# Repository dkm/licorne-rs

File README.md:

# Licorne Smart Alarm Clock

The firmware is pure Rust using [RTIC](https://rtic.rs/)(Real-Time Interrupt-driven Concurrency).

Objectives:
* allow for small kids to be aware of different day period using a simple color code (ie. 5:00 is sleep time).
* continue to learn embedded Rust
* have fun

## Features

* 2.13'in E-Paper display
* DS3231 RTC for keeping track of time
* BME680 for temperature and COV measures
* TI TM4C123G (Cortex M4F)

## Build log

The project initially started during first French lock-down because we really
needed our sleep time and the ours kids could not make the difference between
5:00 and 8:00. A first [Arduino
prototype](https://github.com/dkm/licorne-smartalarmclock) came to life quickly
and has been used for several months. In parallel, this project started with no
hard deadline with the following goals:
- have a more finished hardware solution (versus previous arduino breadboard)
- use event-based programming using embedded Rust

## PCB

## Software

## End result

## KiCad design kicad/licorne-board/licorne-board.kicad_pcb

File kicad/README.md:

# Simple Kicad file for making the board using Toner Transfer.

## Reused resources

custom.lib and custom.pretty extracted from Neotron Hardware:
https://github.com/Neotron-Compute/Neotron-32-Hardware/ for the EK-TM4C123GXL
board symbol and footprint.

Both items are covered by Creative Commons [CC-BY-SA 4.0]:

```
This schematic and PCB design is Copyright (c) Jonathan 'theJPster' Pallant and other Neotron 32 contributors.

This work is licensed under a Creative Commons Attribution-ShareAlike 4.0 International License.
```
[CC-BY-SA 4.0]:https://creativecommons.org/licenses/by-sa/4.0/legalcode

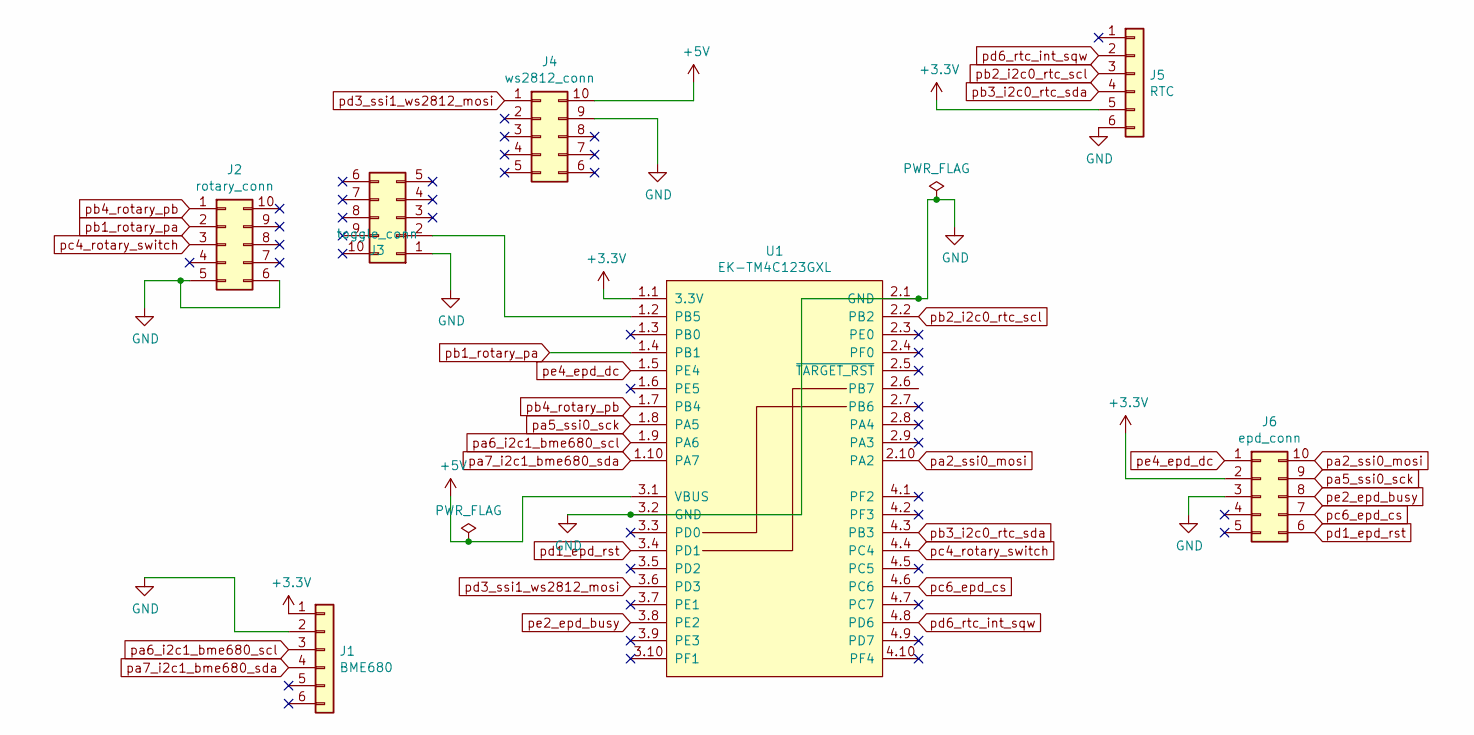
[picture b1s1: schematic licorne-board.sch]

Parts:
J1: BME680; PinHeader_1x06_P2.54mm_Vertical
J2: rotary_conn; IDC-Header_2x05_P2.54mm_Vertical
J3: toggle_conn; IDC-Header_2x05_P2.54mm_Vertical
J4: ws2812_conn; IDC-Header_2x05_P2.54mm_Vertical
J5: RTC; PinHeader_1x06_P2.54mm_Vertical
J6: epd_conn; IDC-Header_2x05_P2.54mm_Vertical
U1: EK-TM4C123GXL; Launchpad_4x10

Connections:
+3V3: J1.1, J5.5, J6.2, U1.1.1 (3.3V)
+5V: J4.10, U1.3.1 (VBUS)
GND: J1.2, J2.5, J2.6, J3.1, J4.9, J5.6, J6.3, U1.2.1 (GND), U1.3.2 (GND)
unnamed: J3.2, U1.1.2 (PB5)
pa2_ssi0_mosi: J6.10, U1.2.10 (PA2)
pa5_ssi0_sck: J6.9, U1.1.8 (PA5)
pa6_i2c1_bme680_scl: J1.3, U1.1.9 (PA6)
pa7_i2c1_bme680_sda: J1.4, U1.1.10 (PA7)
pb1_rotary_pa: J2.2, U1.1.4 (PB1)
pb2_i2c0_rtc_scl: J5.3, U1.2.2 (PB2)
pb3_i2c0_rtc_sda: J5.4, U1.4.3 (PB3~)
pb4_rotary_pb: J2.1, U1.1.7 (PB4)
pc4_rotary_switch: J2.3, U1.4.4 (PC4)
pc6_epd_cs: J6.7, U1.4.6 (PC6)
pd1_epd_rst: J6.6, U1.3.4 (PD1)
pd3_ssi1_ws2812_mosi: J4.1, U1.3.6 (PD3)
pd6_rtc_int_sqw: J5.2, U1.4.8 (PD6)
pe2_epd_busy: J6.8, U1.3.8 (PE2)
pe4_epd_dc: J6.1, U1.1.5 (PE4)

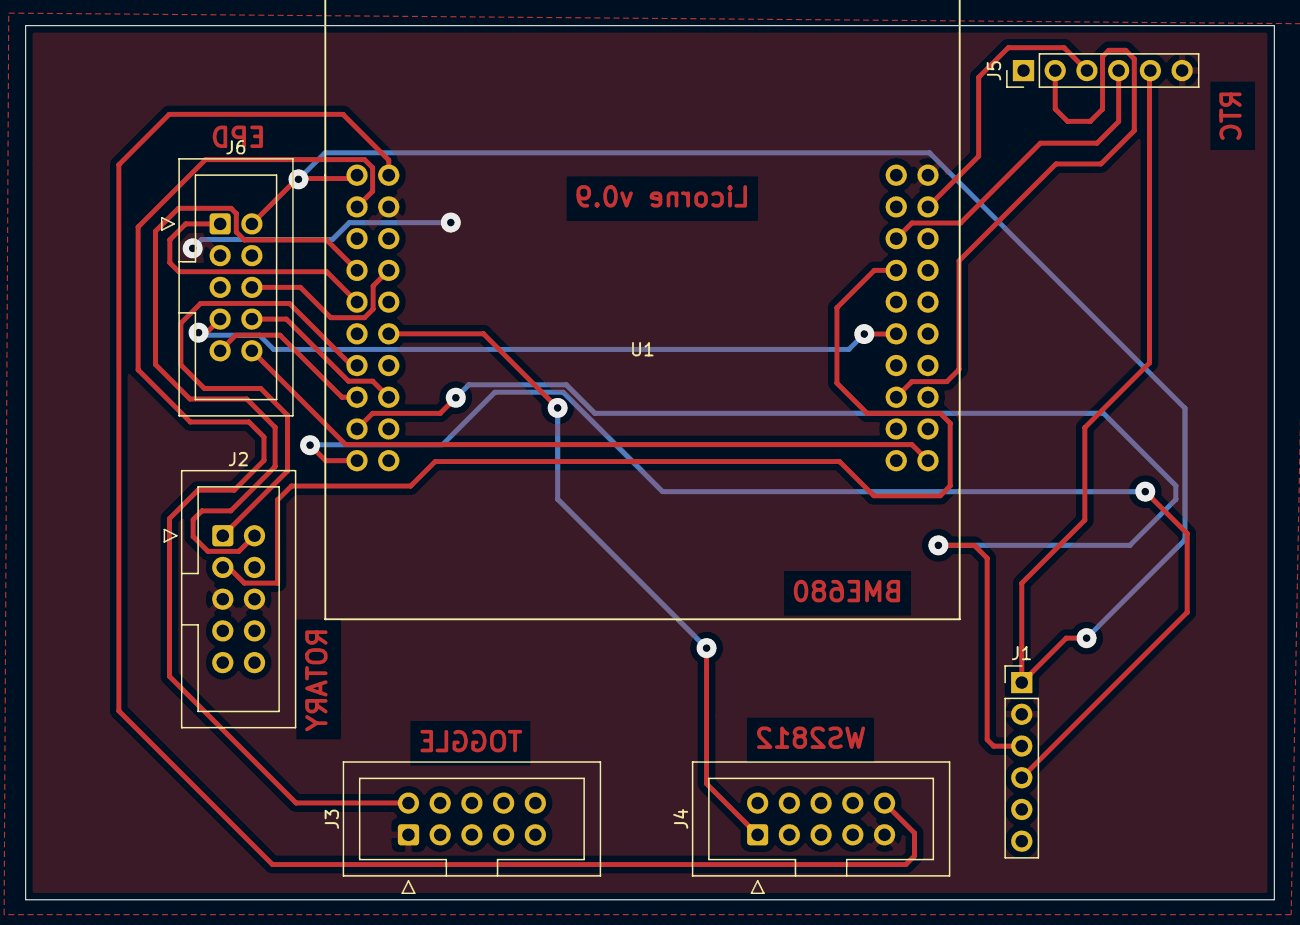
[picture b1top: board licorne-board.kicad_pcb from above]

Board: 2 copper layers, 100.0 x 70.0 mm, 7 parts (0 on the bottom side), 19 nets.

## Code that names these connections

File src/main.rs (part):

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    }
}

// Beware that PB7/PD1 and PB6/PD0 pairs are connected by a 0-ohm resistor
// You need to unsolder these R if you want to use both pins in a pair.
//
// PA2: SSI0 [epd]
// PA4: SSI0 [epd unconnected]
// PA5: SSI0 [epd]
// PA6: I2C1 (scl) [bme680]
// PA7: I2C1 (sca) [bme680]
//
//
// PB1: Rotary Encoder (pinA)
// PB2: I2C0 (SCL) [rtc]
// PB3: I2C0 (SDA) [rtc]
// PB4: Rotary Encoder (pinB)
// PB5: Toggle Switch (config mode)
// PB6:
// PC4: Rotary switch
//
// PC6: GPIO [EPD-cs]
//
// PD0: SSI1 [WS2812 unconnected]
// PD1: [EPD-reset]
// PD2: SSI1 [WS2812 unconnected]
// PD3: SSI1 [WS2812 DIN]
// PD6: RTC / INT
//
// PE2: GPIO Floating [EPD-busy]
// PE4: [EPD-dc]

use ds323x::{Ds323x, NaiveTime};
use tm4c123x_hal::{
    gpio::gpioa::{PA2, PA4, PA5, PA6, PA7},
    gpio::gpiob::{PB1, PB2, PB3, PB4, PB5},
    gpio::gpioc::{PC4, PC6},
    gpio::gpiod::{PD0, PD1, PD2, PD3},
    gpio::gpioe::{PE2, PE4},
    gpio::{
        AlternateFunction, Floating, Input, OpenDrain, Output, PullDown, PullUp, PushPull, AF2, AF3,
    },
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type I2c0T = I2c<
    I2C0,
    (
        PB2<AlternateFunction<AF3, PushPull>>,
        PB3<AlternateFunction<AF3, OpenDrain<Floating>>>,
    ),
>;

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type I2c1T = I2c<
    I2C1,
    (
        PA6<AlternateFunction<AF3, PushPull>>,
        PA7<AlternateFunction<AF3, OpenDrain<Floating>>>,
    ),
>;

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type Spi0T = Spi<
    SSI0,
    (
        PA2<AlternateFunction<AF2, PushPull>>,
        PA4<AlternateFunction<AF2, PushPull>>,
        PA5<AlternateFunction<AF2, PullDown>>,
    ),
>;

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    (
        PD0<AlternateFunction<AF2, PushPull>>,
        PD2<AlternateFunction<AF2, PushPull>>,
        PD3<AlternateFunction<AF2, PullDown>>,
    ),
>;

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
pub type EpdT = Epd2in13<
    Spi0T,
    PC6<Output<PushPull>>,
    PE2<Input<Floating>>,
    PE4<Output<PushPull>>,
    PD1<Output<PushPull>>,
    SimpleAsmDelay,
>;

type RotaryT = Rotary<PB1<Input<PullUp>>, PB4<Input<PullUp>>>;

#[derive(PartialEq)]
pub struct TimeRange {
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    brightness: u8,
}

type ToggleSwitchPinT = PB5<Input<PullUp>>;
type ToggleSwitchT = Switch<ToggleSwitchPinT>;

type RotarySwitchPinT = PC4<Input<PullUp>>;
type RotarySwitchT = Switch<RotarySwitchPinT>;

#[rtic::app(device = tm4c123x_hal::pac, peripherals = true, dispatchers = [UART1, UART2, UART3, UART4])]
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//    use rtic::cyccnt::Instant;

    use tm4c123x_hal::{
        gpio::{gpiod::PD6, Floating, GpioExt, Input, InterruptMode, PullUp, AF2, AF3},
        i2c::I2c,
        spi::{Spi, MODE_0},
        sysctl::{self, SysctlExt},
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        display_dirty: bool,

        #[cfg(feature = "rtc")]
        rtc_int_pin: PD6<Input<PullUp>>,

        // ws2812
        leds: LedsT,
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        let i2c_rtc_dev = I2c::i2c0(
            p.I2C0,
            (
                portb.pb2.into_af_push_pull::<AF3>(&mut portb.control), // SCL
                portb
                    .pb3
                    .into_af_open_drain::<AF3, Floating>(&mut portb.control),
            ), // SDA
            100.khz(),
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        let mut spi0 = Spi::spi0(
            p.SSI0,
            (
                porta.pa2.into_af_push_pull::<AF2>(&mut porta.control), // SCK
                porta.pa4.into_af_push_pull::<AF2>(&mut porta.control), // Miso
                porta.pa5.into_af_pull_down::<AF2>(&mut porta.control), // Mosi
            ), // Mosi
            MODE_0,
            2_000_000.hz(),
            &clocks,
            &sc.power_control,
        );
        let cs_pin = portc.pc6.into_push_pull_output(); // cs
        let rst_pin = portd.pd1.into_push_pull_output();
        let dc_pin = porte.pe4.into_push_pull_output(); // dc
        let busy_pin = porte.pe2.into_floating_input();

        #[cfg(feature = "bme")]
        let i2c_bme680 = I2c::i2c1(
            p.I2C1,
            (
                porta.pa6.into_af_push_pull::<AF3>(&mut porta.control), // SCL
                porta
                    .pa7
                    .into_af_open_drain::<AF3, Floating>(&mut porta.control),
            ), // SDA
            100.khz(),
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            (
                portd.pd0.into_af_push_pull::<AF2>(&mut portd.control), // SCK
                portd.pd2.into_af_push_pull::<AF2>(&mut portd.control), // Miso
                portd.pd3.into_af_pull_down::<AF2>(&mut portd.control), // Mosi (connected)
            ), // Mosi
            ws2812::MODE,
            3_000_000.hz(),
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
        let leds = ws2812::Ws2812::new(spi_ws2812);

        let rot_pinA = portb.pb1.into_pull_up_input();
        let rot_pinB = portb.pb4.into_pull_up_input();

        let rotary = Rotary::new(rot_pinA, rot_pinB);
        let rotary_pin = portc.pc4.into_pull_up_input();

        // GPIO for interrupt
        // SQW/INT pin wired to PD6
        #[cfg(feature = "rtc")]
        let mut rtc_int_pin = portd.pd6.into_pull_up_input();

        #[cfg(feature = "rtc")]
        let ranges;
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        }

        // switch is using PUR, is_low() <=> pressed <=> 'true' state
        let toggle_pin = portb.pb5.into_pull_up_input();
        let toggle_init_state = toggle_pin.is_high().unwrap();
        let mut toggle_switch = ToggleSwitchT::new(toggle_pin, toggle_init_state);
        toggle_switch
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
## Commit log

2020-06-17 First commit for first working version
    The smartclock is mostly working as expected. Looks like
    there is something not so stable with I2C but that's most
    likely cause by tm4c123 hal support crate.
    It relies on a modified version of ds323x crate until I
    can upstream the change or do these differently.
2020-06-28 Change default cargo target
    Also, use gdb-multiarch as cargo runner, as it's the easiest for Debian.
2020-07-16 Update cargo deps
2020-07-18 Initial work for interrupt driven alarms
    Use INT pin from DS3231 for raising an interrupt.
2020-07-19 Use interrupt for triggering alarms
    Move away from polling and use interrupts.
    Next step would be to add support for hibernation module of TM4C (and fix i2c).
2020-07-21 Make the CortexM4 go to sleep between alarms
    Between 2 events, force the core to stop executing any insn until the next IRQ
    is raised.
2020-07-22 Minor fixes
    Remove useless import or useless statement.
2020-07-22 use github actions
2020-07-22 Refactor imports
    Remove some useless import, rearrange others.
2020-10-01 display hour
2020-10-03 WIP: clock, display, events
    Correctly display clock, suspend screen between events, clean warnings.
2020-11-08 Kind of works, but will move to RTIC
2020-11-08 WIP for RTIC port
2020-11-09 WIP for porting to RTIC
2020-11-12 Use some cfg feature to enable/disable semihosting prints
2020-11-12 Still WIP. Can be flashed without problem
    Clock is updated every minutes with a full e-ink refresh.
    LEDs should be correctly set from Range info
    +Some debug info displayed.
2020-11-15 Add rotary encoder + fmt
2020-11-16 Use rotary encoder.
    Currently only spawns a task.
2020-11-17 Add a toggle switch in the mix !
    But won't work as RTIC uses SYST for periodic task... and tm4c-hal also uses
    SYST for implementing Delay, needed for EPD.
    Does not build.
2020-11-18 Toggle button works to switch from config to normal mode
    There is still an issue when starting with switch in config mode.
    Mode change should be refactored.
2020-11-18 Refactored the mode change and how leds are handled
    Currently, Config mode will rotate the leds with the rotary encoder.
    RTC IT should be made lower prio than config task.
2020-11-20 Refactor some types, add rotary switch handler
    Wrap data needed for debouncing a switch in Switch struct.
2020-11-22 Various WIP
    Config can cycle hour/minute change by pressing rotary.
    Going back from config to normal using toggle saves new time in RTC.
    Leave out partial refresh of EPD for now.
2020-11-23 Add bme680 support. Only init for now
2020-11-23 Only display time on EPD
2020-11-25 Support for bme680
    Init and sensor read using I2C working.
2020-11-26 Basic layout of all info on screen
    Looks like there is no bigger font than 24x32, so I may need to draw custom
    chars for numbers.
2020-11-29 Refresh Cargo deps, fix a bunch of warnings.
2020-11-29 Use digital::v2 instead of obsolete digital::v1
    ... and add corresponding .unwrap()
2020-11-29 Better layout for time, count i2c error for bme680
    Looks like my prototype has something wrong with bme680.
    Sensor stops reponding sometimes and a full hw reset is needed.
    Handle errors and count them (until a reset is done...)
2020-11-29 Use partial refresh instead of full refresh
    Still need to to a full refresh at least once a day.
2020-12-02 Partial refresh for screen
2020-12-04 Rework partial refresh
    split screen and display resources. Have epd and bme share the same prio level
    as we don't want any loop delay to be interrupted.
2020-12-05 First shot at making conditional compilation for bme680
    'usedrogue' cargo feature can be used to use drogue-bme680 instead of bme680.
    Currently, works better as it reports a temperature value.
2020-12-05 Use embedded-various-fonts from git
2020-12-05 Fix tm4c123x dep
2020-12-05 Cross compile various config
2020-12-09 Simple board.
    Not yet tested, first version.
2020-12-09 Use NaiveTime during configuration.
2020-12-09 Minor cosmetic and cleanups
    Reindent, use fewer LEDs during testing, fix wiring comments, fix range checking
    during init.
2020-12-09 Use smooth LEDs transitions
2020-12-09 Workaround bme680 problem
    The sensors becomes unresponsive after some time (can be quick, can be very
    long) until a reset is done. Using a soft reset seems to be working, but most
    likely there's something incorrect elsewhere.
2020-12-09 Add one more config for GH action
2020-12-13 Use upstream rotary-encoder crate
2020-12-13 Change EPD busy pin from PB0 et PC6
    Strange behavior observed on EPD, changing pin to avoid problems with using a
    GPIO port also used with interrupt. Should not change anything... and it does
    not change anything.
2020-12-13 Forcing Full refresh until EPD strange behavior fixed
    Using Full refresh does not make the incorrect behavior go away, but it makes
    the device still usable. Not a fix nor a workaround.
2020-12-13 Changed overall state change monitoring
    Rotary encoder+switch are not monitor when state is not Configuration(_).
    When entering configuration mode, start a polling task for both rotary encoder
    and switch (no more interrupt here).
    Toggle switch is still monitored using interrupt: a debounce task is started
    when an IT is raised and the task is not already running/queued.
2020-12-14 Migrate to RTIC 0.6 (alpha)
    Refactor for RTIC 0.6.
    Change tasks priorities as this is most certainly the underlying problem.
    Party drop support for bme680 crate, only use drogue's crate now.
2020-12-15 Switch to RTIC master
    Until next release or something breaks.
2021-01-07 Drop support for bme680 crate
    Only support the drogue one as it seems to work better.
2021-01-07 Refactor and clean
    Reorder task in priority order for easier read.
    refresh_time does not always refresh the EPD, avoiding some priority problem
    that led to uncorrect behavior.
2021-01-27 More modular app
    Nearly possible to enable/disable epd,bme and rtc parts.
    gpiod ISR still need to be commented, so not only via cargo features.
    Rewired rotary switch from PB7 to PC4 as it's shorting the board. Most probably
    the pin can't be used like this on the stellaris board (should better check).
2021-01-27 Bug fix for range checking during init
    range that cross a day need special care.
    Also fix wiring comment and import after change for rotary switch pin.
2021-01-27 Handle brightness and allow for change in config mode
    Config now cycles between hour, minute and brightness.
    Leds data now wrapped in a struct with everything needed inside.
    Re-enable partial refresh by setting the refresh count to 200 until a full
    refresh must be done.
2021-02-02 New version of PCB
    Routing done on larger area.
2021-02-02 Fix range checking, lower brightness by default
    Range checking was incorrect for range crossing day.
2021-02-04 Change footprint for bme680 and rtc
    Do not use ISC connector and solder module directly on PCB.
2021-02-04 Add more config in github actions
    Build more configs.
2021-02-10 WIP doc
2021-02-13 pcb: Fix typo in label name
    Armless typo in pin name for EPD SPI clock.
2021-02-21 Make config more usable
    Make config loop frequency higher (2s -> 100ms).
    Use simple dirty bool to skip refresh when nothing has changed. Currently
    handles both epd and leds, but should be split. LEDs are a bit longer to refresh
    and can overflow the queue (1-sized).
2021-02-27 Bump cortex-m version
2021-02-27 Minor code cleanup
    Remove old/unused commented code
2021-02-27 Better handling of EPD refresh during configuration
    Use a dirty flag to only update EPD when something has changed.
    Makes the rotary use more friendly. Still not perfect as we miss all event
    during a refresh... The less refresh, the less lost events...
2021-02-27 Use devel branch for epd-waveshare
2021-02-27 Display range name when active
    Range's name is displayed when active below the time.
2021-07-06 Have more sensible default feature set
    Use screen, RTC and bme sensor by default
2021-07-08 WIP update crates version
    Now builds.
